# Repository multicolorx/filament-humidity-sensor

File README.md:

# Filament Humidity Sensor

Battery-powered filament storage humidity monitor based on `STM32L053` + `SHT40`, with segmented LCD drive and Li-ion power input.

## Overview

This repository contains the hardware design files and supporting firmware for a compact humidity sensor intended for filament storage monitoring.

The board is built around:
- `STM32L053R8T6` low-power MCU (with LCD segment peripheral)
- `SHT40-CD1B-R3` digital humidity/temperature sensor (`I2C`)
- Single-cell Li-ion input (`18650` compatible)
- Onboard battery protection (`DW01A` + `UMW8205A`)
- `TCR2LF33` 3.3 V LDO regulator
- Segmented LCD interface via two 1x5 headers

## Repository Layout

- [Schematic](hardware/kicad/filament-humidity-sensor.kicad_sch)
- [PCB layout](hardware/kicad/filament-humidity-sensor.kicad_pcb)
- [KiCad project](hardware/kicad/filament-humidity-sensor.kicad_pro)
- [Gerber files](hardware/gerbers/rev001/)
- [Gerber zip release](hardware/gerbers/gerbers-rev001.zip)
- [Datasheets](hardware/datasheets/)
- [Example firmware](firmware/low-power-example/)

See [hardware/README.md](hardware/README.md) for the hardware-specific file index.

## Hardware Interfaces

### Battery Input

- `J1` (`1x01`, 2.54 mm): `BAT+`
- `J2` (`1x01`, 2.54 mm): `BAT-`

### SWD Programming Header (`J5`, 1x05, 2.54 mm)

1. `+3V3`
2. `SWDIO`
3. `GND`
4. `SWCLK`
5. `NRST`

Use an ST-Link compatible probe for programming/debugging.

### LCD Headers

`J3` (`1x05`, 2.00 mm)
1. `LCD_SEG5`
2. `LCD_COM0`
3. `LCD_COM1`
4. `LCD_COM2`
5. `LCD_COM3`

`J4` (`1x05`, 2.00 mm)
1. `LCD_SEG0`
2. `LCD_SEG1`
3. `LCD_SEG2`
4. `LCD_SEG3`
5. `LCD_SEG4`

## Getting Started

1. Open `hardware/kicad/filament-humidity-sensor.kicad_pro` in KiCad 9.
2. Inspect schematic and run ERC.
3. Open PCB and run DRC.
4. Generate Gerber files.
5. Generate drill files.
6. Generate pick-and-place files (if assembly is planned).

## Firmware

Example firmware is available in `firmware/low-power-example/`:
- `firmware/low-power-example/main.c` low-power control loop (SHT40 + LCD + RTC alarm + STOP mode)
- `firmware/low-power-example/README.md` integration notes for STM32CubeMX/CubeIDE

## Notes

- The design uses a single-cell Li-ion source; follow proper battery safety practices.
- Verify connector orientation and pin 1 markings before first power-up.
- Review the datasheets in `hardware/datasheets/` before ordering parts or assembling prototypes.

## License

This project is licensed under `GPL-3.0` (see `LICENSE`).

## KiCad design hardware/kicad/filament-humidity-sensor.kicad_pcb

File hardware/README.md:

# Hardware

This directory contains the PCB design files, release gerbers, and supporting component datasheets for the filament humidity sensor.

## Quick Links

- [Schematic source](kicad/filament-humidity-sensor.kicad_sch)
- [PCB layout source](kicad/filament-humidity-sensor.kicad_pcb)
- [KiCad project](kicad/filament-humidity-sensor.kicad_pro)
- [Gerber and drill files](gerbers/rev001/)
- [Zipped Gerber release](gerbers/gerbers-rev001.zip)
- [Component datasheets](datasheets/)

## Layout

- `kicad/` editable KiCad project files
- `gerbers/` manufacturing outputs
- `datasheets/` PDFs and text notes for selected components
- `backups/` KiCad backup archives

Open the KiCad project with KiCad 9 or newer.

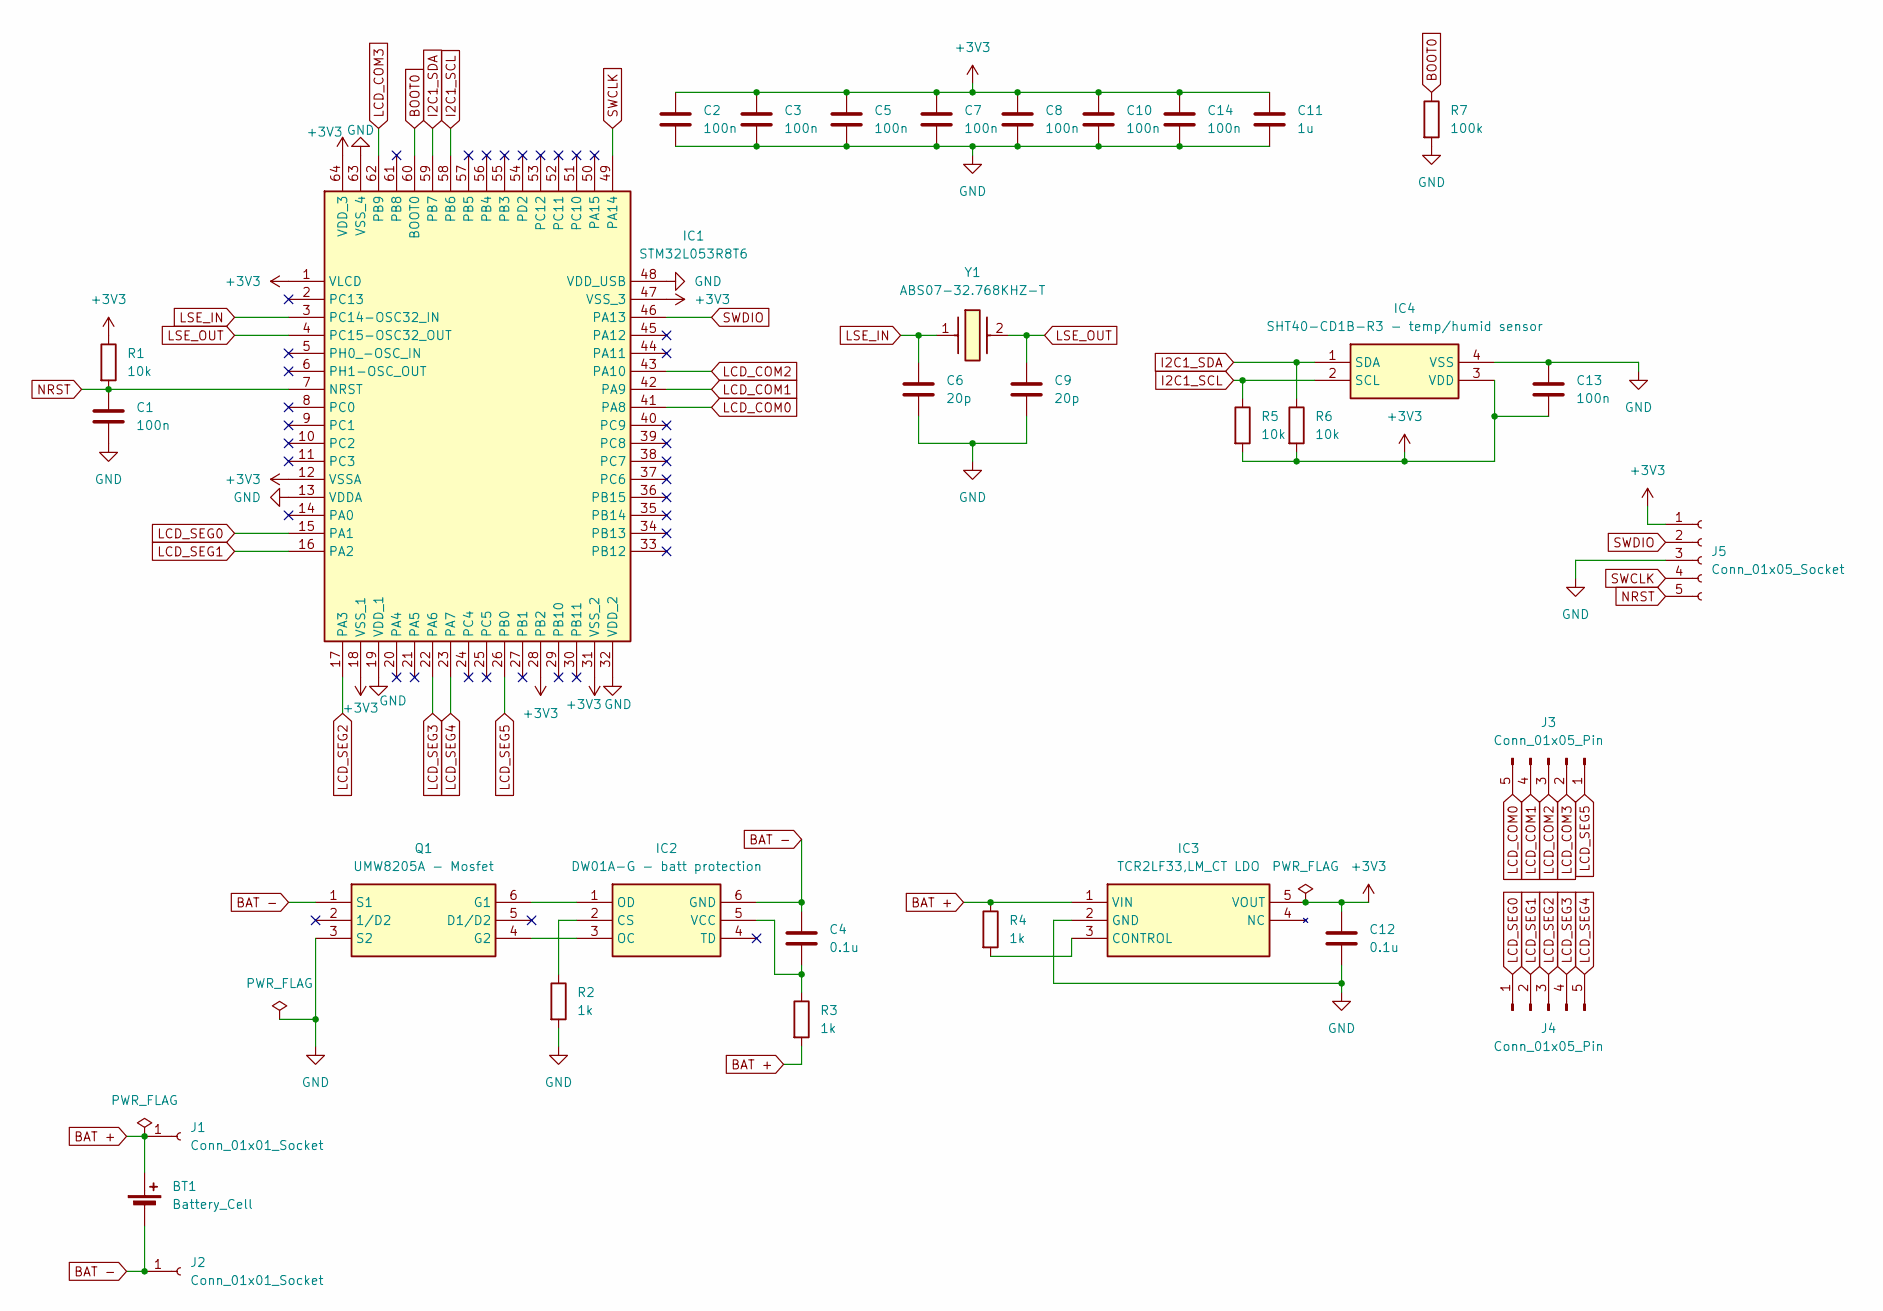
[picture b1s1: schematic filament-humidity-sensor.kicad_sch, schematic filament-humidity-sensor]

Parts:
BT1: Battery_Cell
C1, C2, C3, C5, C7, C8, C10, C13, C14: 100n; C_0805_2012Metric
C4, C12: 0.1u; C_0805_2012Metric
C6, C9: 20p; C_0805_2012Metric
C11: 1u; C_0805_2012Metric
IC1: STM32L053R8T6; QFP50P1200X1200X160-64N; Mouser Part Number 511-STM32L053R8T6
IC2: DW01A-G - batt protection; SOT95P190X145-6N; Manufacturer_Part_Number DW01A-G
IC3: TCR2LF33,LM_CT LDO; TCR2LF33LMCT; Mouser Part Number 757-TCR2LF33LMCT
IC4: SHT40-CD1B-R3 - temp/humid sensor; SHT40CD1BR3; Mouser Part Number 403-SHT40-CD1B-R3
J1, J2: Conn_01x01_Socket; PinHeader_1x01_P2.54mm_Vertical
J3, J4: Conn_01x05_Pin; PinHeader_1x05_P2.00mm_Vertical
J5: Conn_01x05_Socket; PinHeader_1x05_P2.54mm_Vertical
Q1: UMW8205A - Mosfet; SOT95P285X140-6N; Manufacturer_Part_Number UMW8205A
R1, R5, R6: 10k; R_0805_2012Metric
R2, R3, R4: 1k; R_0805_2012Metric
R7: 100k; R_0805_2012Metric
Y1: ABS07-32.768KHZ-T; ABS07; Manufacturer_Part_Number ABS07-32.768KHZ-T; Mouser Part Number 815-ABS07-32.768KHZT

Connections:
+3V3: C2.1, C3.1, C5.1, C7.1, C8.1, C10.1, C11.1, C12.1, C13.2, C14.1, IC1.1 (VLCD), IC1.12 (VSSA), IC1.18 (VSS_1), IC1.28 (PB2), IC1.31 (VSS_2), IC1.47 (VSS_3), IC1.64 (VDD_3), IC3.5 (VOUT), IC4.3 (VDD), J5.1, R1.1, R5.2, R6.2
BAT +: BT1.1 (+), IC3.1 (VIN), J1.1, R3.2, R4.1
BAT -: BT1.2 (-), C4.1, IC2.6 (GND), J2.1, Q1.1 (S1)
BOOT0: IC1.60 (BOOT0), R7.1
GND: C1.2, C2.2, C3.2, C5.2, C6.2, C7.2, C8.2, C9.2, C10.2, C11.2, C12.2, C13.1, C14.2, IC1.13 (VDDA), IC1.19 (VDD_1), IC1.32 (VDD_2), IC1.48 (VDD_USB), IC1.63 (VSS_4), IC3.2 (GND), IC4.4 (VSS), J5.3, Q1.3 (S2), R2.2, R7.2
I2C1_SCL: IC1.58 (PB6), IC4.2 (SCL), R5.1
I2C1_SDA: IC1.59 (PB7), IC4.1 (SDA), R6.1
LCD_COM0: IC1.41 (PA8), J3.5
LCD_COM1: IC1.42 (PA9), J3.4
LCD_COM2: IC1.43 (PA10), J3.3
LCD_COM3: IC1.62 (PB9), J3.2
LCD_SEG0: IC1.15 (PA1), J4.1
LCD_SEG1: IC1.16 (PA2), J4.2
LCD_SEG2: IC1.17 (PA3), J4.3
LCD_SEG3: IC1.22 (PA6), J4.4
LCD_SEG4: IC1.23 (PA7), J4.5
LCD_SEG5: IC1.26 (PB0), J3.1
LSE_IN: C6.1, IC1.3 (PC14-OSC32_IN), Y1.1
LSE_OUT: C9.1, IC1.4 (PC15-OSC32_OUT), Y1.2
NRST: C1.1, IC1.7 (NRST), J5.5, R1.2
unnamed: IC2.2 (CS), R2.1
unnamed: IC2.3 (OC), Q1.4 (G2)
unnamed: IC2.1 (OD), Q1.6 (G1)
unnamed: C4.2, IC2.5 (VCC), R3.1
unnamed: IC3.3 (CONTROL), R4.2
SWCLK: IC1.49 (PA14), J5.4
SWDIO: IC1.46 (PA13), J5.2

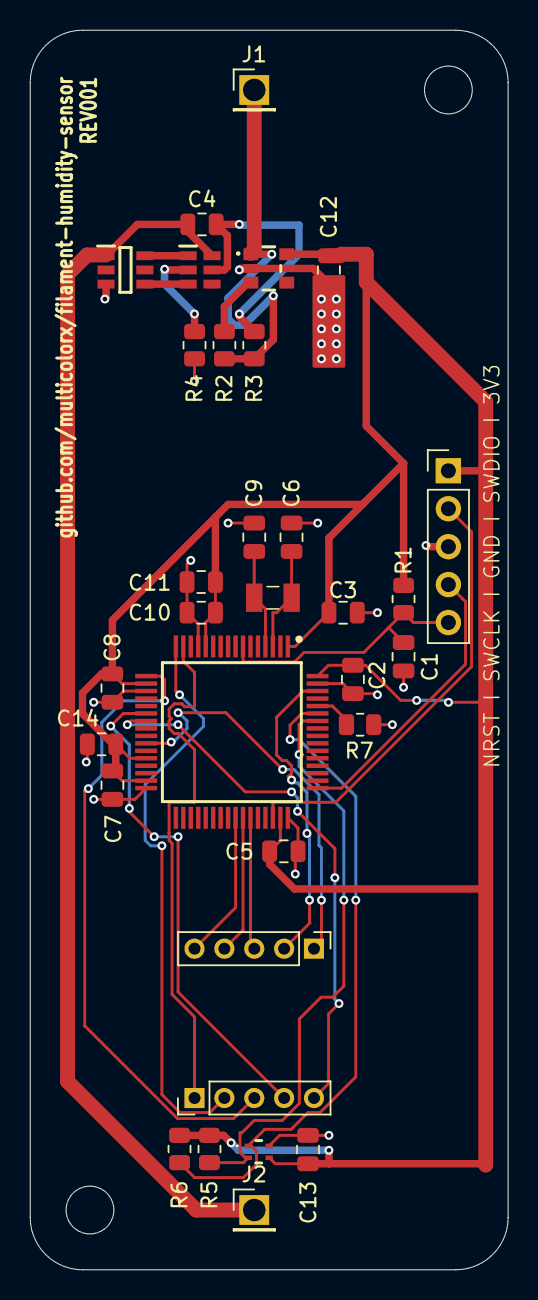
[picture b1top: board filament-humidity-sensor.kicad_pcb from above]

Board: 2 copper layers, 32.0 x 83.0 mm, 32 parts (0 on the bottom side), 27 nets.

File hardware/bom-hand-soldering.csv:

Qty,References,Part,Value,Package_or_Footprint,Hand_Soldering_Note
11,"C1,C2,C3,C4,C5,C7,C8,C10,C12,C13,C14","Ceramic capacitor","100 nF / 0.1 uF","0805","Easy"
1,"C11","Ceramic capacitor","1 uF","0805","Easy"
2,"C6,C9","Crystal load capacitor","20 pF","0805","Easy"
3,"R1,R5,R6","Resistor","10 k","0805","Easy"
3,"R2,R3,R4","Resistor","1 k","0805","Easy"
1,"R7","Resistor","100 k","0805","Easy"
1,"Y1","32.768 kHz crystal","ABS07-32.768KHZ-T","ABS07","Moderate"
1,"IC2","Battery protection IC","DW01A-G","SOT-23-6","Moderate"
1,"Q1","Dual MOSFET","UMW8205A","SOT-23-6","Moderate"
1,"IC3","3.3 V LDO regulator","TCR2LF33,LM_CT","Small SMD regulator package","Moderate"
1,"IC4","Temperature / humidity sensor","SHT40-CD1B-R3","SHT40 compact no-lead package","Hard"
1,"IC1","MCU","STM32L053R8T6","LQFP-64","Moderate to hard"
2,"J1,J2","Battery connection points","Conn_01x01","PinHeader_1x01_P2.54mm_Vertical","Very easy"
2,"J3,J4","LCD headers","Conn_01x05","PinHeader_1x05_P2.00mm_Vertical","Very easy"
1,"J5","SWD programming header","Conn_01x05","PinHeader_1x05_P2.54mm_Vertical","Very easy"
1,"BT1","External battery source","Battery_Cell","No PCB footprint assigned","Off-board item"

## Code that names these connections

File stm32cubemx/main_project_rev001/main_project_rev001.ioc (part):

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Mcu.Name=STM32L053R(6-8)Tx
Mcu.Package=LQFP64
Mcu.UserName=STM32L053R8Tx
PA1.Mode=SEG0
PA1.Signal=LCD_SEG0
PA10.Mode=1/4 Duty Cycle
PA10.Signal=LCD_COM2
PA13.Mode=Serial_Wire
PA13.Signal=SYS_SWDIO
PA14.Mode=Serial_Wire
PA14.Signal=SYS_SWCLK
PA2.Mode=SEG1
PA2.Signal=LCD_SEG1
PA3.Mode=SEG2
PA3.Signal=LCD_SEG2
PA6.Mode=SEG3
PA6.Signal=LCD_SEG3
PA7.Mode=SEG4
PA7.Signal=LCD_SEG4
PA8.Mode=1/4 Duty Cycle
PA8.Signal=LCD_COM0
PA9.Mode=1/4 Duty Cycle
PA9.Signal=LCD_COM1
PB0.Mode=SEG5
PB0.Signal=LCD_SEG5
PB2.Mode=VLCD2
PB2.Signal=LCD_VLCD2
PB6.Mode=I2C
PB6.Signal=I2C1_SCL
PB7.Mode=I2C
PB7.Signal=I2C1_SDA
PB9.Mode=1/4 Duty Cycle
PB9.Signal=LCD_COM3
PC14-OSC32_IN.Mode=LSE-External-Oscillator
PC14-OSC32_IN.Signal=RCC_OSC32_IN
PC15-OSC32_OUT.Mode=LSE-External-Oscillator
PC15-OSC32_OUT.Signal=RCC_OSC32_OUT
RCC.HSE_VALUE=8000000
RCC.SYSCLKFreq_VALUE=2097000
board=custom

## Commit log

2026-02-12 added datasheets and kicad files
2026-02-12 readme
2026-02-12 firmware templates, codex
2026-02-12 er, codex
2026-03-04 stm32
2026-03-18 Add main_project_rev001 and update nucleo_lcd_test_2
2026-04-07 Reorganize hardware files for GitHub
2026-04-07 Add hand-soldering BOM
